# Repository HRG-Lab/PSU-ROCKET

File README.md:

# PSU-ROCKET

## Test Spectra
Plots of test data generated from [Test Spectra](./data/test_spectra.csv)

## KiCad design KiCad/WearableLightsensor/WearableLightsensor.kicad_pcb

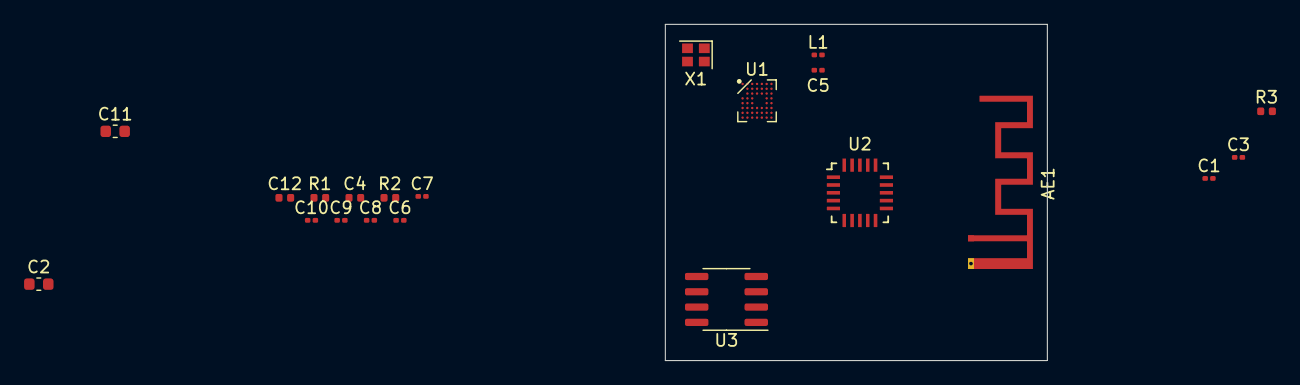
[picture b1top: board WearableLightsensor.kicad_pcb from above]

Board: 4 copper layers, 31.8 x 27.9 mm, 22 parts (1 on the bottom side), 18 nets, no tracks yet.

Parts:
AE1: Antenna; Texas_SWRA117D_2.4GHz_Left
BT1: Battery; BatteryHolder_MPD_BC2003_1x2032
C1, C3, C10: 100nF; C_0201_0603Metric
C2: 4.7uF; C_0603_1608Metric
C4: 1.0uF; C_0402_1005Metric
C5: 1.0pF; C_0201_0603Metric
C6, C7: 12pF; C_0201_0603Metric
C8, C9: 100pF; C_0201_0603Metric
C11: 10uF; C_0603_1608Metric
C12: 1uF; C_0402_1005Metric
L1: 3.3nH; L_0201_0603Metric
R1: 10K; C_0402_1005Metric
R2: DNP; C_0402_1005Metric
R3: 0R; C_0402_1005Metric
U1: nRF52832_WLCSP; BGA-56_7x8_2.956x3.226mm
U2: AS7262; AMS_LGA-20_4.7x4.5mm_P0.65mm
U3: AT25SF081; SOIC-8_3.9x4.9mm_P1.27mm
X1: 32MHz; Crystal_SMD_2016-4Pin_2.0x1.6mm

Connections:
GND: BT1.2, C1.2, C2.2, C3.2, C4.2, C5.1, C6.1, C7.1, C8.1, C9.1, C10.1, C11.1, C12.2, R3.2, U1.C4, U1.C5, U1.D2, U1.E3, U1.F5, U2.16, U3.4
unnamed: AE1.1, L1.2
unnamed: C1.1, U1.B7
unnamed: C4.1, U1.A6
unnamed: C5.2, L1.1, U1.D1
unnamed: C6.2, U1.A1, X1.1
unnamed: C7.2, U1.B2, X1.2
unnamed: C8.2, U1.C2
unnamed: C9.2, U1.A2
unnamed: R1.2, U2.2
unnamed: R2.2, R3.1, U2.8
unnamed: U1.E1, U2.11
unnamed: U1.E2, U2.12
unnamed: U2.3, U3.6
unnamed: U2.4, U3.5
unnamed: U2.5, U3.2
unnamed: U2.6, U3.1
VDD: BT1.1, C2.1, C3.1, C10.2, C11.2, C12.1, R1.1, R2.1, U1.A7, U1.H7, U2.14, U2.17, U3.3, U3.7, U3.8

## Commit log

2020-03-30 Add files via upload
    The .csv file contains normalized spectra for a fluorescent fixture and the LEDCube array in 1nm increments
    In the .xlsx file, I also included the melanopic curve, 5nm SPDs, and a brief colorimetric summary including a calculation of Melanopic Lux
2020-03-30 Add files via upload
    The two competing methods for calculating the circadian activity of specific lighting conditions
2020-04-10 Add test spectra plot
2020-04-10 Fix relative links
2020-04-10 Clean up repo a bit
2020-04-26 Bring up pycom board
2020-04-26 Work on melanopic flux algorithm
2020-05-15 Add script to read from sensor for testing
2020-05-26 Sensor Array and CL-500A Measurements
    5 light sources (daylight, linear fluorescent, compact fluorescent, RBL LED, and RGBAW+UV LED) were measured using two sensor orientations (vertically with light sources within field of view, and hor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
2020-06-06 Start Wearable Sensor Schematic
2020-06-22 Implement nRF52832 reference design
2020-07-06 Finalize schematic. Begin work on layout
2020-07-06 Revert to QFN package. There is enough room
2020-07-06 Fix uP symbol and make schematic pass ERC
